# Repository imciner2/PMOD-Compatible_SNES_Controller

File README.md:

# PMOD-Compatible_SNES_Controller
A Pmod(tm) Compatible SNES controller connector.

This circuit board is designed to interface a SNES controller to a circuit board containing Digilent Pmod(tm) ports. This circuit board complies with the Digielnt Pmod(tm) Interface Specification found here: https://www.digilentinc.com/Pmods/Digilent-Pmod_%20Interface_Specification.pdf.

This project makes use of a 3rd party SNES connector supplied by Raphnet Technologies. It is part number 250025 and can be found here: http://raphnet-tech.com/products/snes_controller_connector/index.php

## Library Housekeeping

### To read in any changes from the Kicad library repository to this one:

1. Fetch the changes

    ``` git fetch libraries ```

2. Merge the changes

    ``` git merge -s subtree --squash libraries/master ```

3. Commit the changes

    ``` git commit -m "Updated libraries directory" ```

### To push any of the changes from this project to the Kicad libarary repository

1. Create commits for the changes (make them seperate from everything else)

2. Create a new branch locally

    ``` git checkout -b library-work libraries/master ```

3. Select the commits to add to the library (The command shown below will use the 5th commit before the current revision, simply modify the 5 to change which commit is referenced)

    ``` git cherry-pick -x --strategy=subtree master~5 ```

4. Push the new changes back to the libraries repository

    ``` git push libraries library-work:master ```

5. Go back to the working repository

    ``` git checkout master ```

6. Delete the branch you just used

    ``` git branch -D library-work ```

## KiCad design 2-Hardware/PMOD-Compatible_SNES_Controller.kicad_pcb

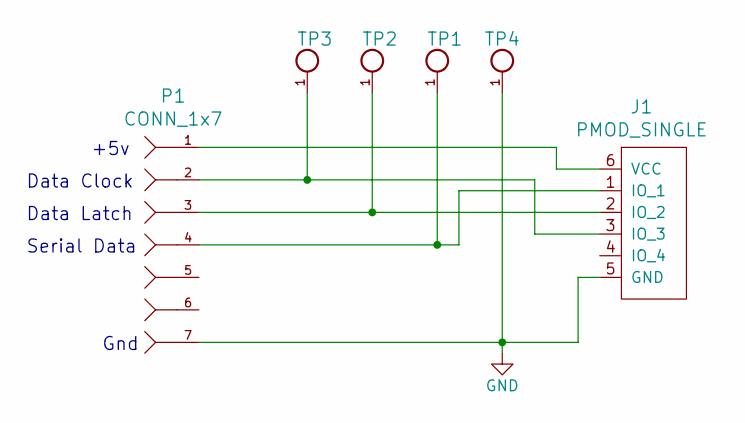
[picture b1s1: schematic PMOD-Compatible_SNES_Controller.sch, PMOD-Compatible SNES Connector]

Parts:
J1: PMOD_SINGLE; PMOD_SINGLE_MALE
P1: CONN_1x7; GAMING_SNES
TP1, TP3: TEST_POINT; TESTPOINT_063; DigikeyNumber Value
TP2, TP4: TEST_POINT; TESTPOINT_063

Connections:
GND: J1.5 (GND), P1.7, TP4.1
unnamed: J1.1 (IO_1), P1.4, TP1.1
unnamed: J1.2 (IO_2), P1.3, TP2.1
unnamed: J1.3 (IO_3), P1.2, TP3.1
unnamed: J1.6 (VCC), P1.1

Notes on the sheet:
+5v
Data Clock
Data Latch
Serial Data
Gnd

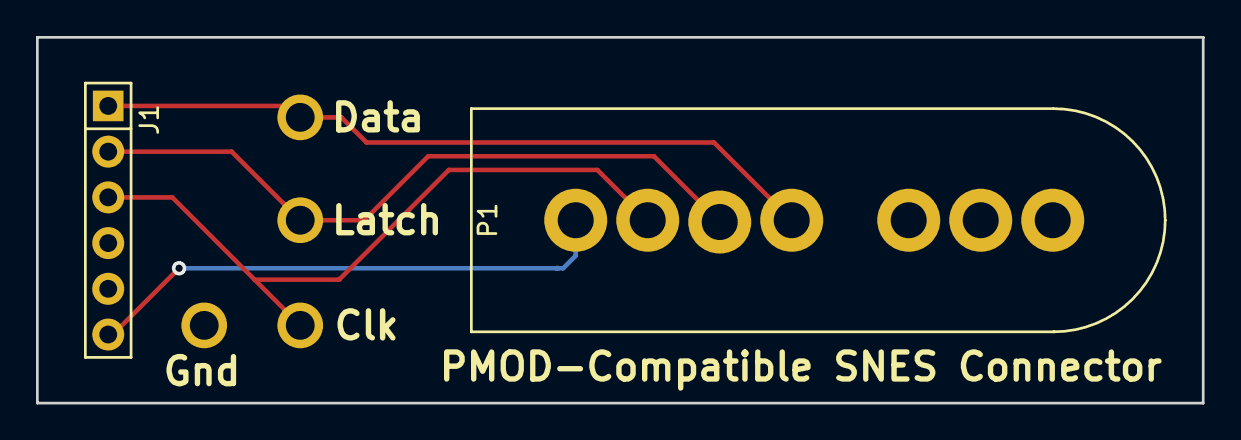
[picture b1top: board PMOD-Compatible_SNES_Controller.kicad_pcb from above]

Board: 2 copper layers, 64.8 x 20.3 mm, 6 parts (0 on the bottom side), 5 nets.

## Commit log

2015-01-24 Update Readme
    Added SNES connector source.
2015-01-24 Added board pattern for the SNES connector
2015-02-19 Updated readme to reflect PMOD licensing agreement
2015-02-19 Added datasheet for the testpoints
2015-07-17 Added git ignore file
2015-07-17 Updated readme file
2015-07-17 Kicad libraries initial commit
2016-11-18 Removed libraries
2016-11-18 Added libraries as submodule
2016-11-18 Started schematic and board
2016-12-28 Updated library
2016-12-28 Rev'ed the board and added testpoint
2017-01-24 Updated PMOD link
2017-05-16 Updated libraries
